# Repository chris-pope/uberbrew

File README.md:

Uber Brewer
=========================

Semi-automated control system for nano breweries.

## Table of Contents

## Hardware

## Software

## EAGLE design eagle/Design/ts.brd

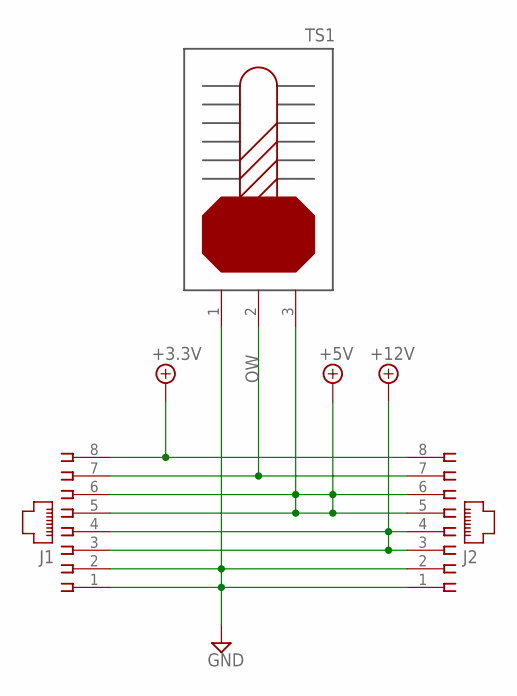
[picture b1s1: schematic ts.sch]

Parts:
J1, J2: 215877-4
TS1: DS18B20; KK-156-3

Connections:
+3P3V: J1.8, J2.8
+5V: J1.5, J1.6, J2.5, J2.6, TS1.3
+12V: J1.3, J1.4, J2.3, J2.4
GND: J1.1, J1.2, J2.1, J2.2, TS1.1
OW: J1.7, J2.7, TS1.2

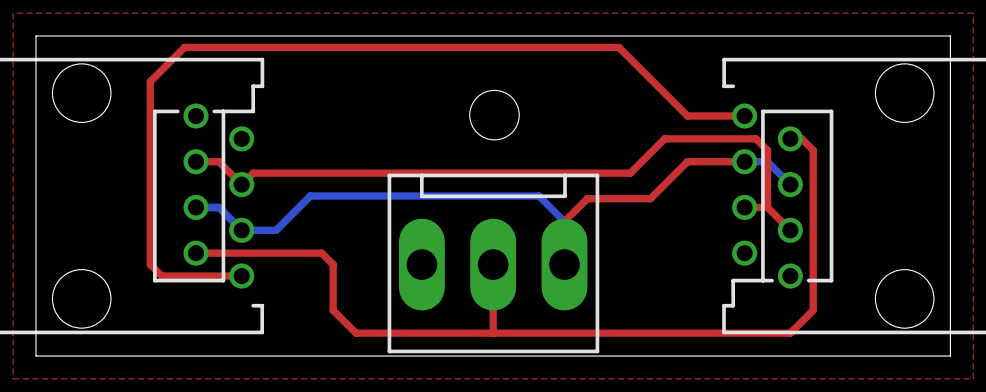
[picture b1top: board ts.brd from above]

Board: 2 copper layers, 50.8 x 17.8 mm, 3 parts (0 on the bottom side), 5 nets.

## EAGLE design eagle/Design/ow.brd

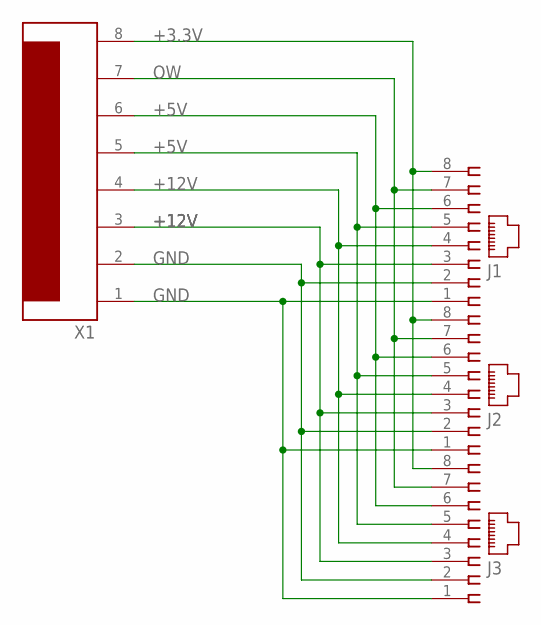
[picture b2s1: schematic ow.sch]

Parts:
J1, J2, J3: 215877-4
X1: 1WIRE-CON; KK-156-8

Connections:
+3.3V: J1.8, J2.8, J3.8, X1.8
+5V: J1.5, J1.6, J2.5, J2.6, J3.5, J3.6, X1.5, X1.6
+12V: J1.3, J1.4, J2.3, J2.4, J3.3, J3.4, X1.3, X1.4
GND: J1.1, J1.2, J2.1, J2.2, J3.1, J3.2, X1.1, X1.2
OW: J1.7, J2.7, J3.7, X1.7

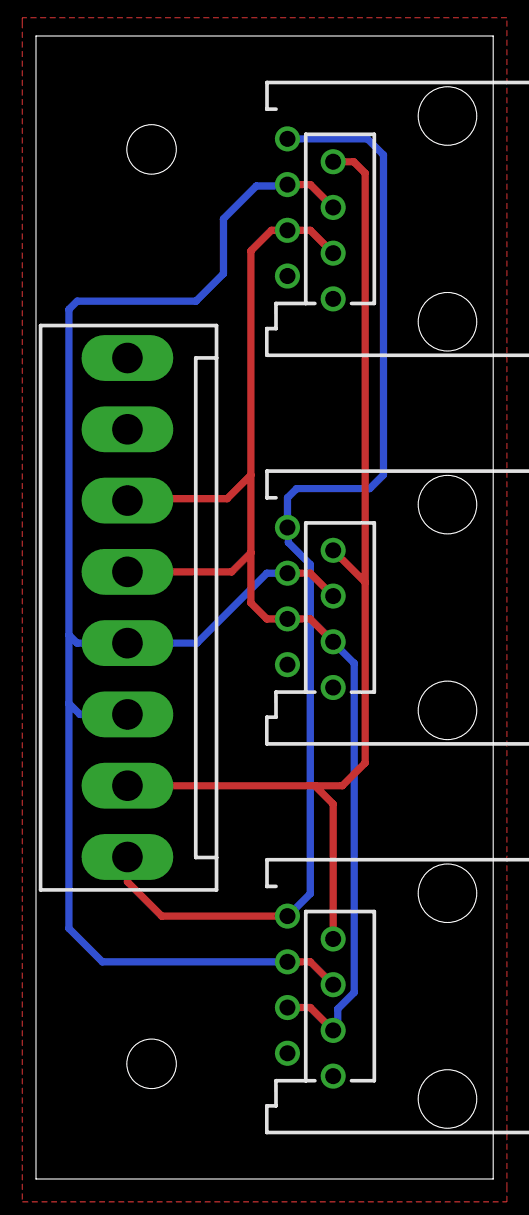
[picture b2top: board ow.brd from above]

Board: 2 copper layers, 25.4 x 63.5 mm, 4 parts (0 on the bottom side), 5 nets.

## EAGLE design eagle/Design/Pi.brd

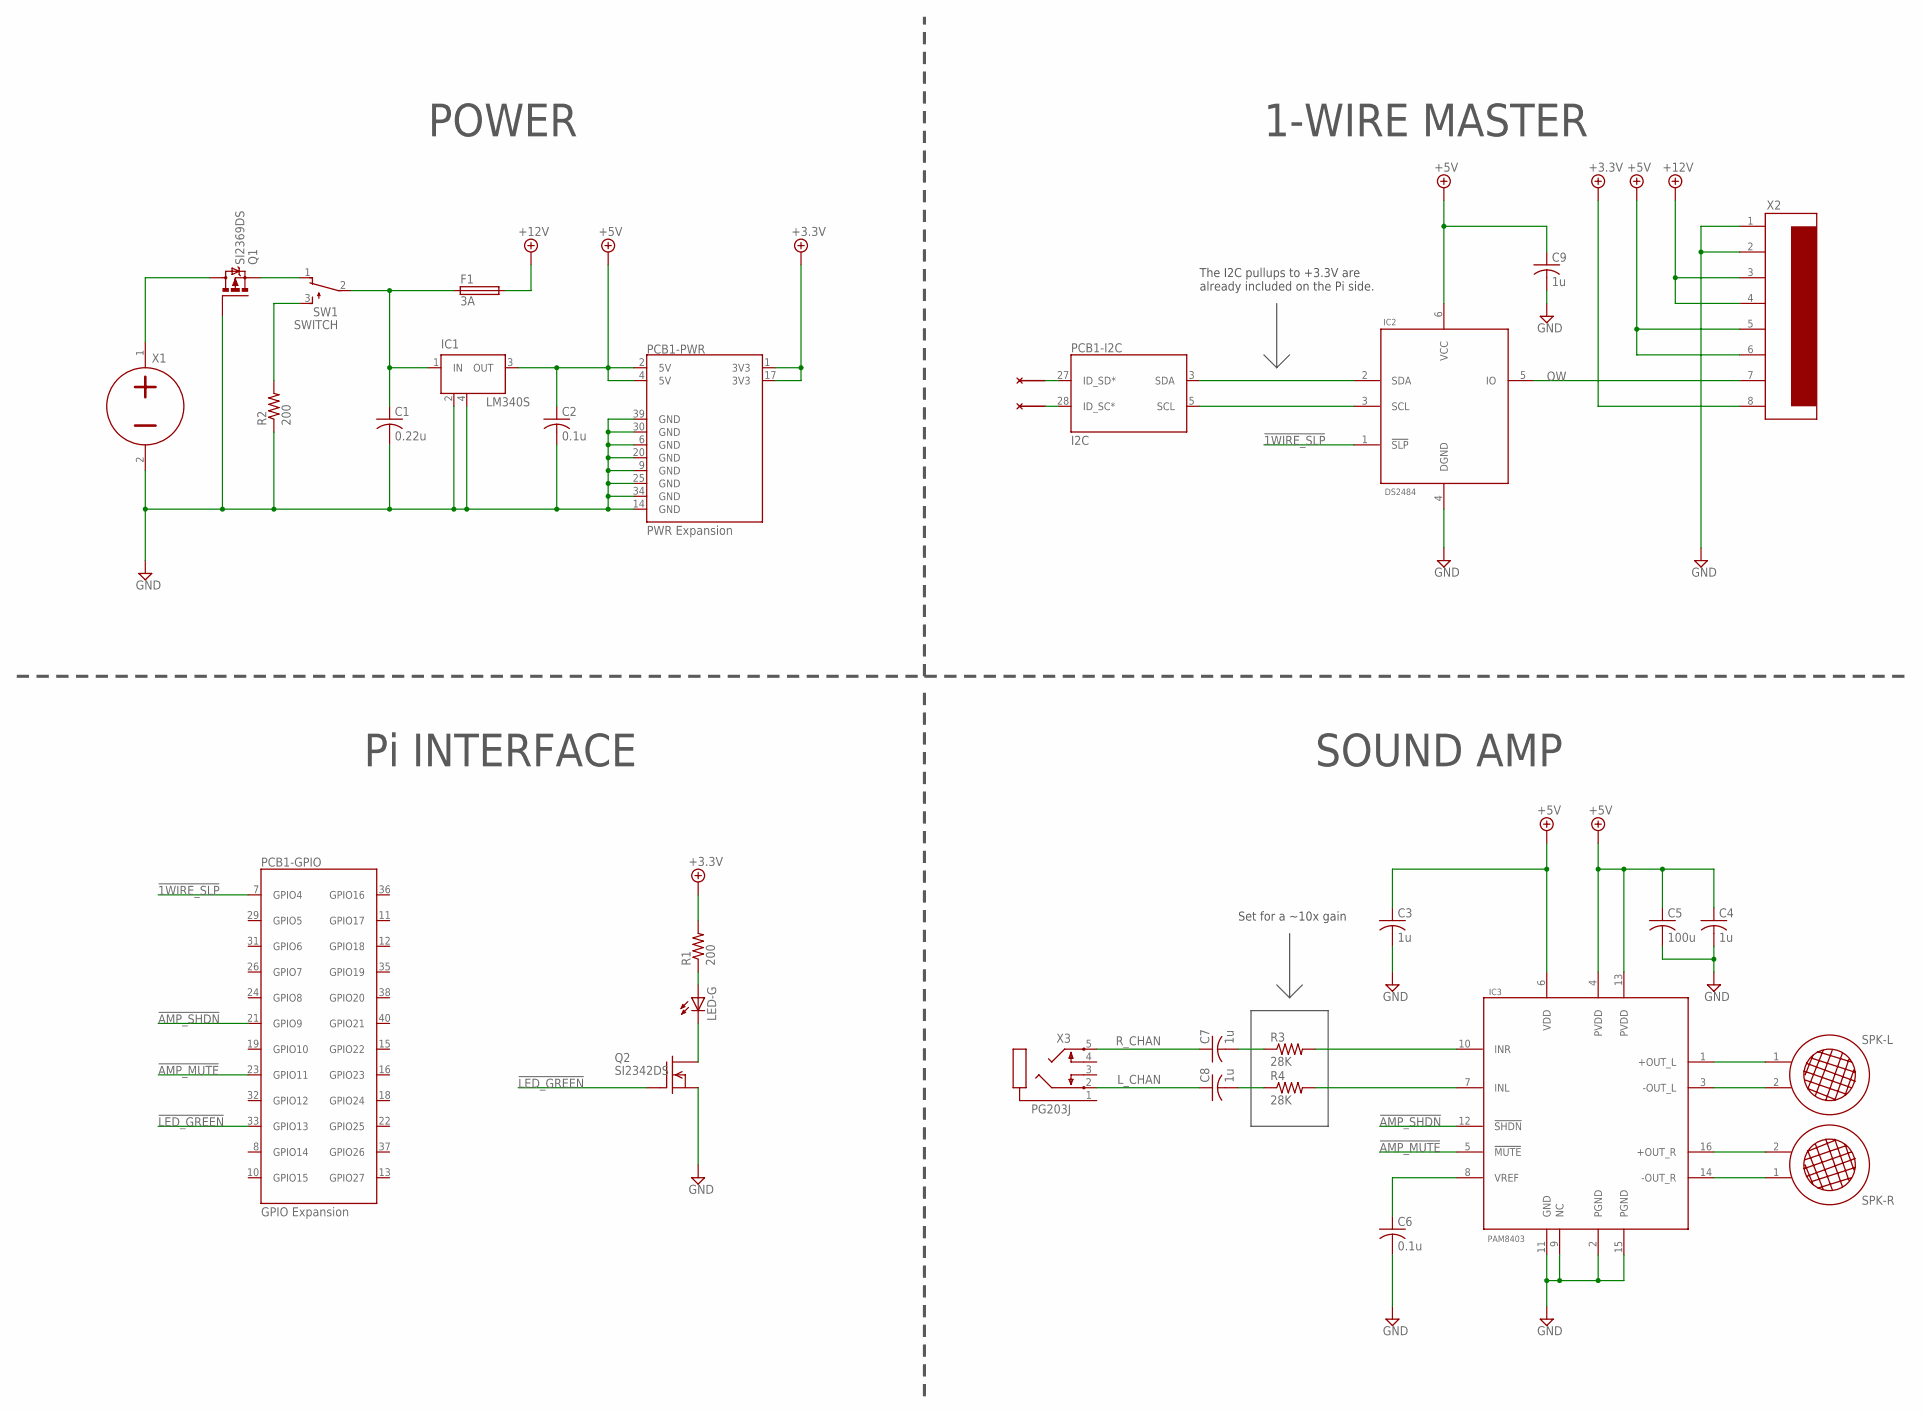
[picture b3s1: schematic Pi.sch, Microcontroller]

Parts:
C1: 0.22u; C0603
C2, C6: 0.1u; C0603
C3, C4, C7, C8, C9: 1u; C0603
C5: 100u; C0805
F1: 3A; F0603
IC1: LM340S; SOT223
IC2: DS2484; SOT23-6L
IC3: PAM8403; SOP16
LED-G: LEDCHIP-LED0603; CHIP-LED0603
PCB1: RPI3
Q1: SI2369DS; SOT23
Q2: SI2342DS; SOT23
R1, R2: 200; R0603
R3, R4: 28K; R0603
SPK-L: SPEAKER; KK-156-2
SPK-R: SPEAKER; KK-156-2
SW1: SWITCH; KK-156-3
X1: SUPPLY_12V; KK-156-2
X2: 1WIRE-CON; KK-156-8
X3: PG203J

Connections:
!1WIRE_SLP: IC2.1 (!SLP), PCB1.7 (GPIO4)
!AMP_MUTE: IC3.5 (!MUTE), PCB1.23 (GPIO11)
!AMP_SHDN: IC3.12 (!SHDN), PCB1.21 (GPIO9)
!LED_GREEN: PCB1.33 (GPIO13), Q2.1 (G)
+3P3V: PCB1.1 (3V3), PCB1.17 (3V3), R1.2, X2.8
+5V: C2.1, C3.1, C4.1, C5.1, C9.1, IC1.3 (OUT), IC2.6 (VCC), IC3.4 (PVDD), IC3.6 (VDD), IC3.13 (PVDD), PCB1.2 (5V), PCB1.4 (5V), X2.5, X2.6
+12V: F1.2, X2.3, X2.4
GND: C1.2, C2.2, C3.2, C4.2, C5.2, C6.2, C9.2, IC1.2 (GND), IC1.4 (GND), IC2.4 (DGND), IC3.2 (PGND), IC3.9 (NC), IC3.11 (GND), IC3.15 (PGND), PCB1.6 (GND), PCB1.9 (GND), PCB1.14 (GND), PCB1.20 (GND), PCB1.25 (GND), PCB1.30 (GND), PCB1.34 (GND), PCB1.39 (GND), Q1.1 (G), Q2.2 (S), R2.1, X1.2, X2.1, X2.2
L_CHAN: C8.1, X3.2
unnamed: LED-G.A, R1.1
unnamed: R2.2, SW1.3 (S)
unnamed: IC2.2 (SDA), PCB1.3 (SDA)
unnamed: IC2.3 (SCL), PCB1.5 (SCL)
unnamed: C6.1, IC3.8 (VREF)
unnamed: Q1.3 (D), X1.1
unnamed: Q1.2 (S), SW1.1 (O)
unnamed: C7.2, R3.1
unnamed: IC3.10 (INR), R3.2
unnamed: C1.1, F1.1, IC1.1 (IN), SW1.2
unnamed: C8.2, R4.1
unnamed: IC3.7 (INL), R4.2
unnamed: IC3.1 (+OUT_L), SPK-L.1
unnamed: IC3.3 (-OUT_L), SPK-L.2
unnamed: IC3.16 (+OUT_R), SPK-R.2
unnamed: IC3.14 (-OUT_R), SPK-R.1
unnamed: LED-G.C, Q2.3 (D)
OW: IC2.5 (IO), X2.7
R_CHAN: C7.1, X3.5

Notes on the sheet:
POWER
Pi INTERFACE
1-WIRE MASTER
The I2C pullups to +3.3V are already included on the Pi side.
Set for a ~10x gain
SOUND AMP

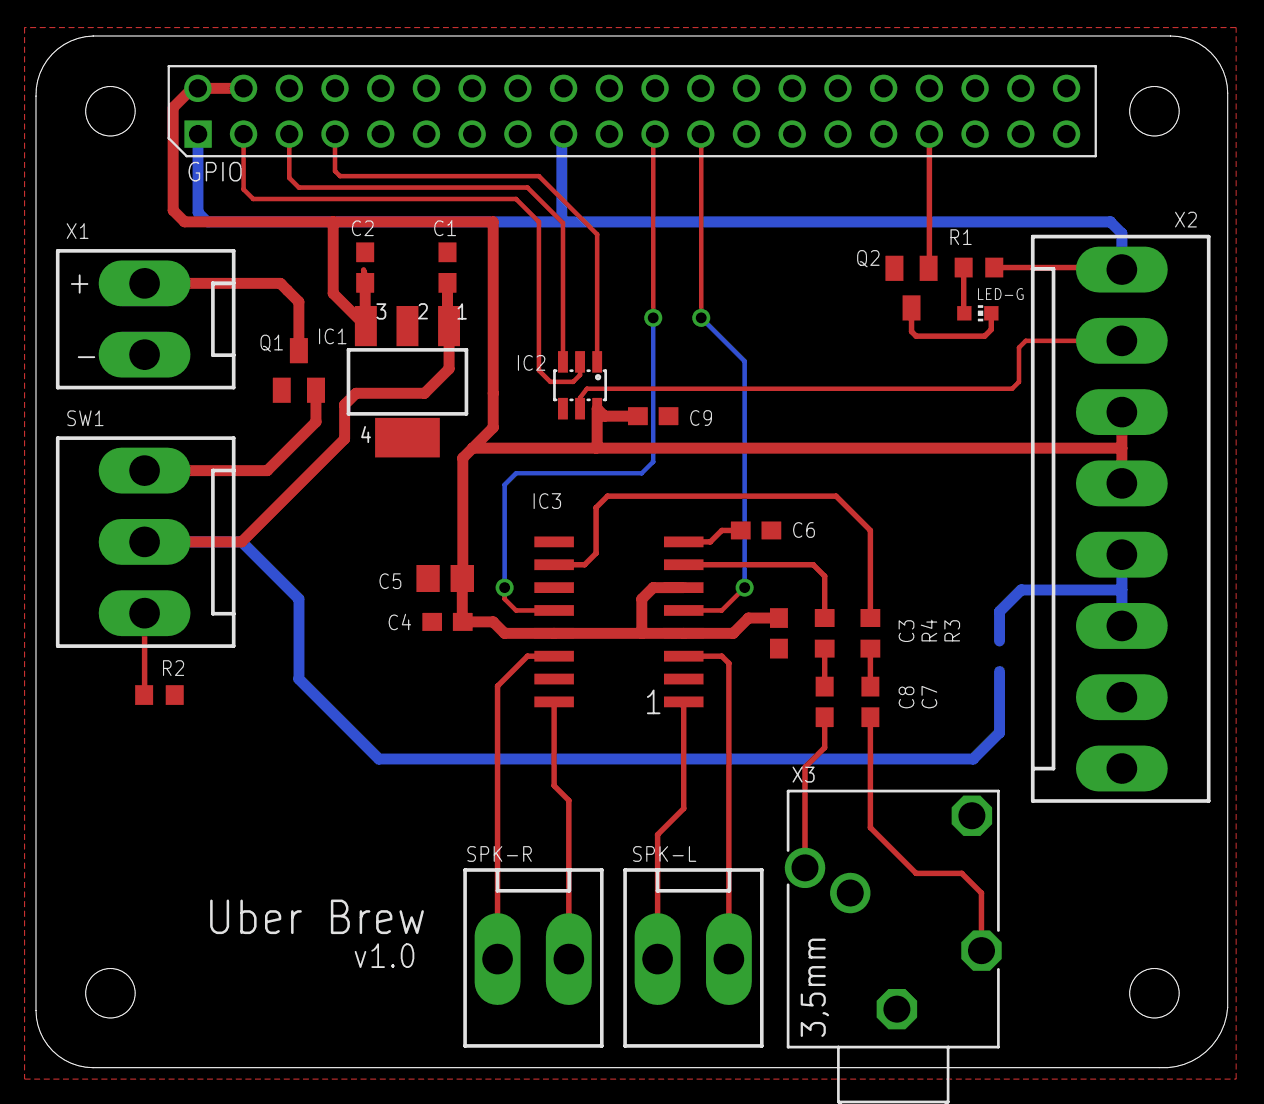
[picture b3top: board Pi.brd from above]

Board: 2 copper layers, 66.2 x 57.3 mm, 27 parts (1 on the bottom side), 28 nets.

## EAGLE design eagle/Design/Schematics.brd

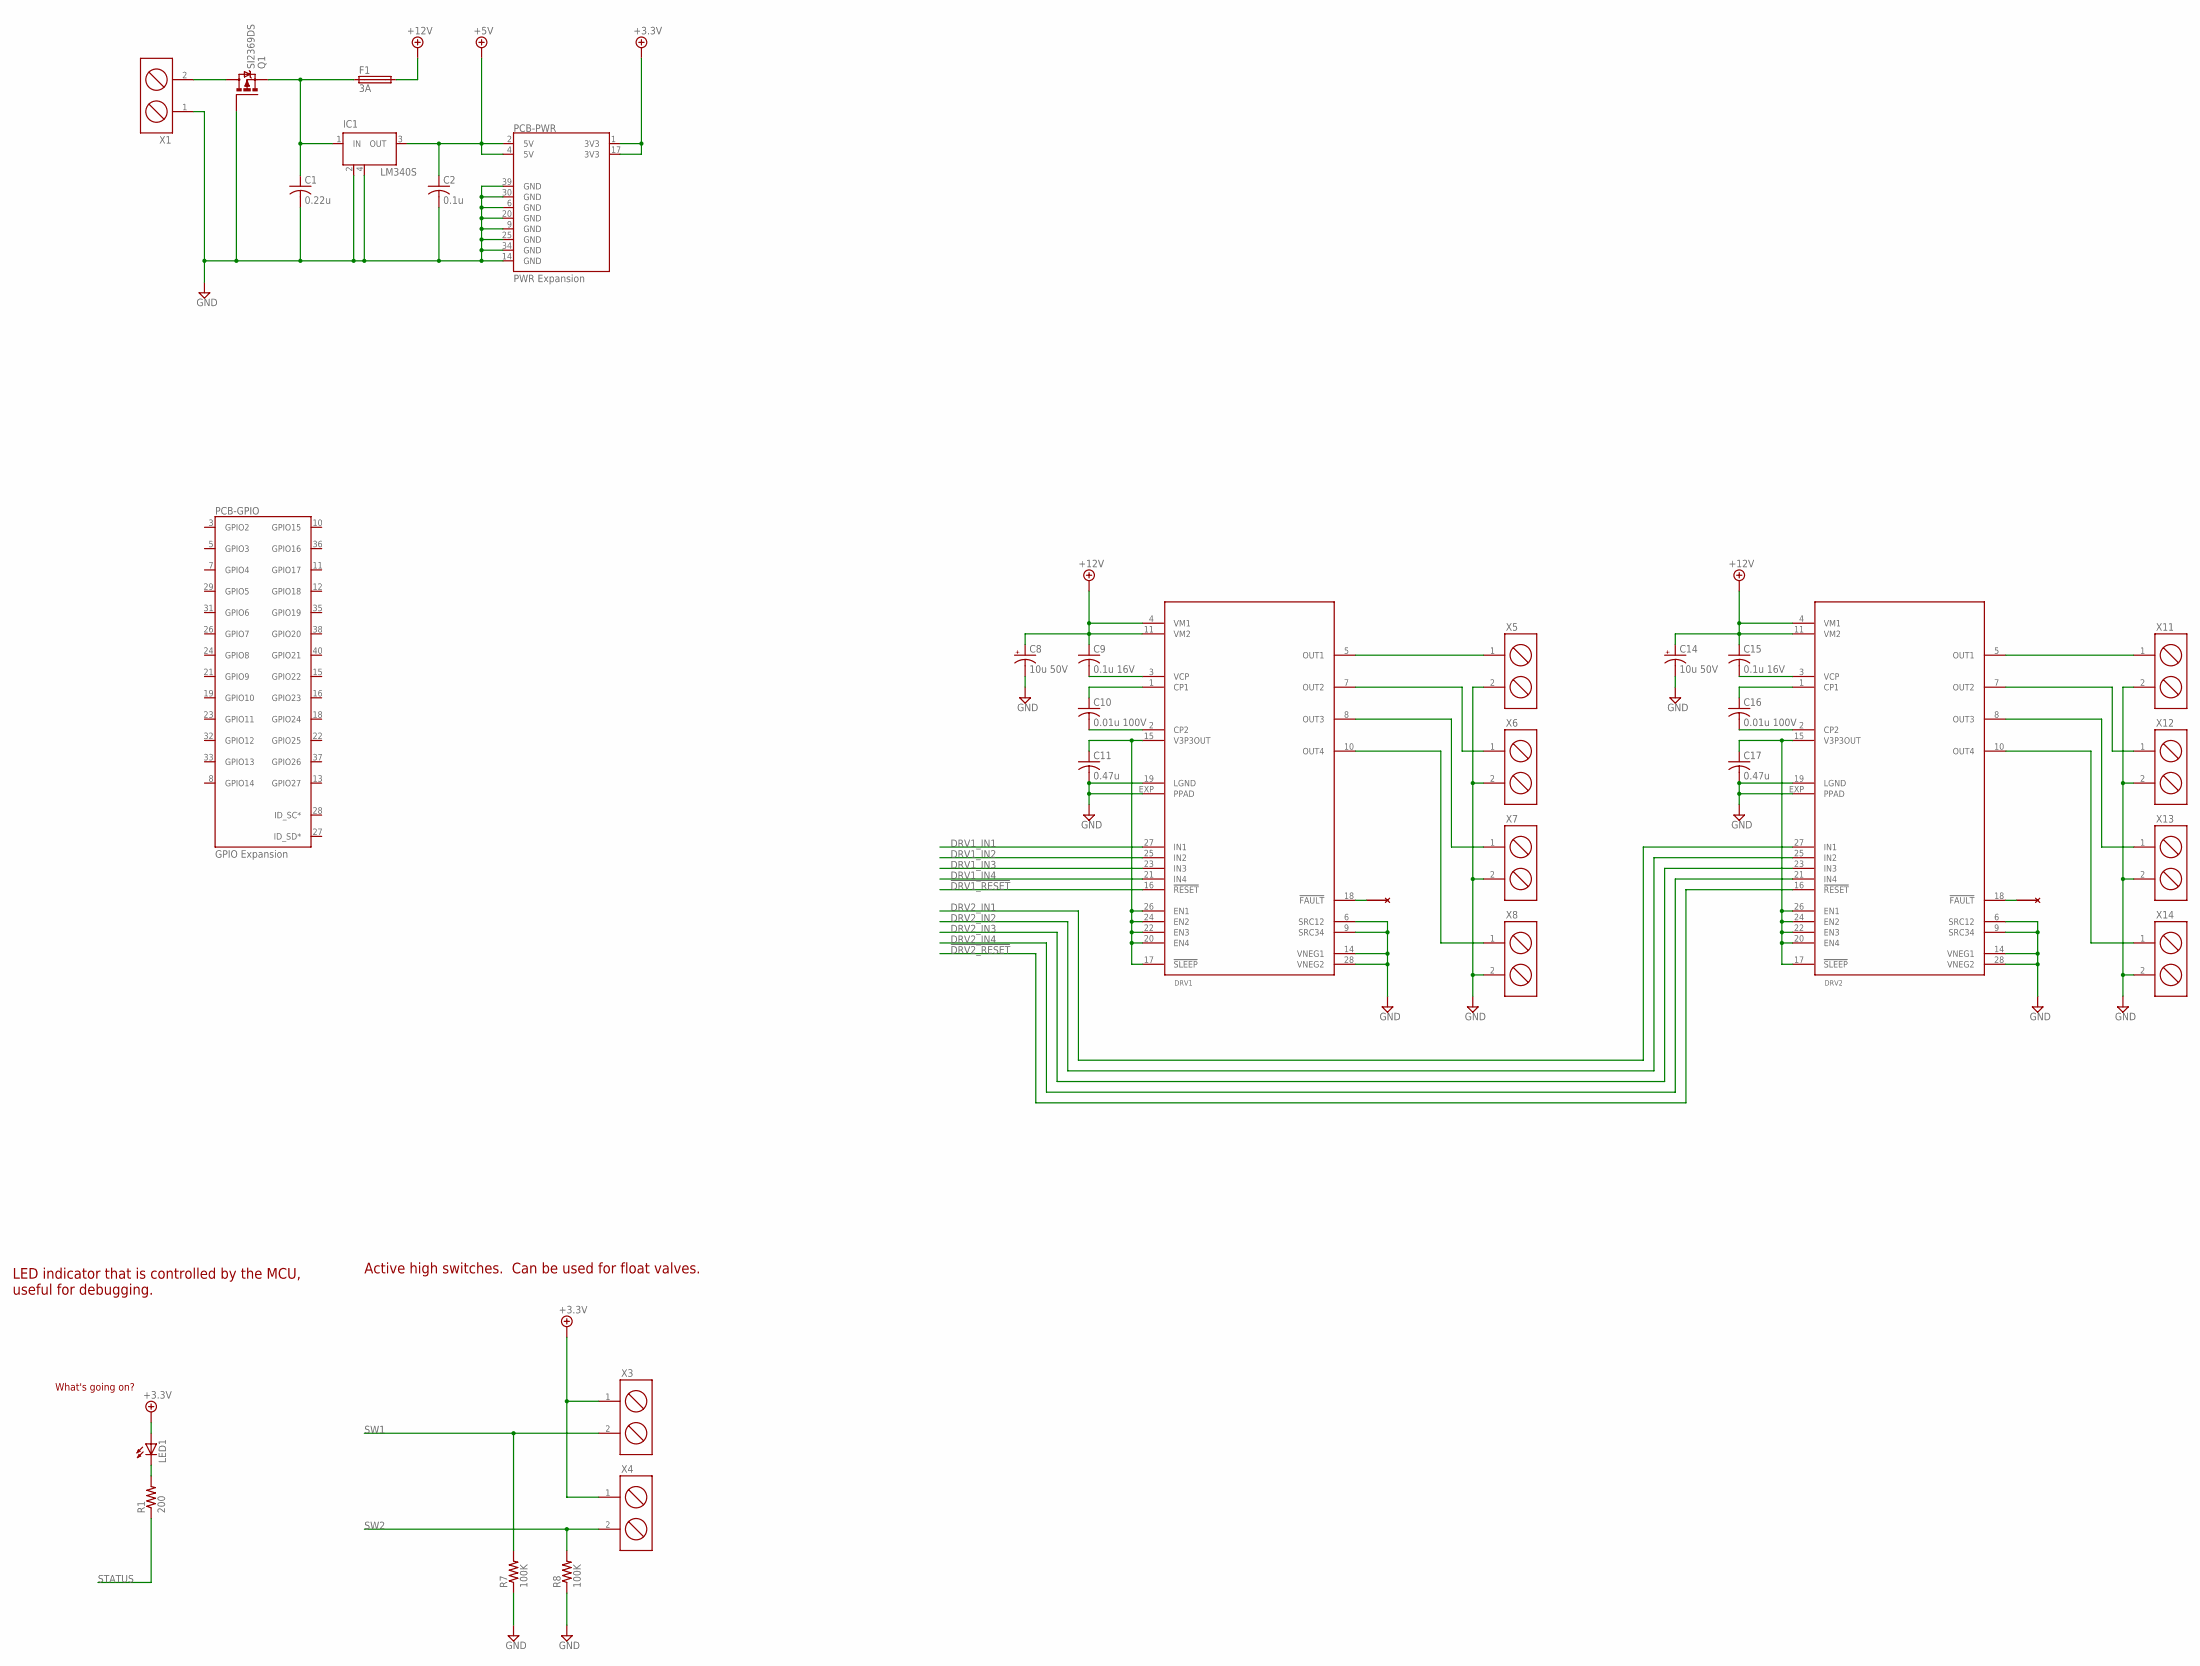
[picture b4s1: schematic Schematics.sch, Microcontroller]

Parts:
C1: 0.22u; C0603
C2: 0.1u; C0603
C8, C14: 10u 50V; TAP5-50
C9, C15: 0.1u 16V; C0603
C10, C16: 0.01u 100V; C0603
C11, C17: 0.47u; C0603
DRV1, DRV2: DRV8844; HTSSOP28PWP
F1: 3A; F0603
IC1: LM340S; SOT223
LED1: LEDCHIP-LED0805; CHIP-LED0805
PCB: RPI3
Q1: SI2369DS; SOT23
R1: 200; R0603
R7, R8: 100K; R0603
X1, X3, X4, X5, X6, X7, X8, X11, X12, X13, X14: MPT2; 2POL254

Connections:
!DRV1_RESET: DRV1.16 (!RESET)
!DRV2_RESET: DRV2.16 (!RESET)
+3P3V: LED1.A, PCB.1 (3V3), PCB.17 (3V3), X3.1, X4.1
+5V: C2.1, IC1.3 (OUT), PCB.2 (5V), PCB.4 (5V)
+12V: C8.+, C9.1, C14.+, C15.1, DRV1.4 (VM1), DRV1.11 (VM2), DRV2.4 (VM1), DRV2.11 (VM2), F1.2
DRV1_IN1: DRV1.27 (IN1)
DRV1_IN2: DRV1.25 (IN2)
DRV1_IN3: DRV1.23 (IN3)
DRV1_IN4: DRV1.21 (IN4)
DRV2_IN1: DRV2.27 (IN1)
DRV2_IN2: DRV2.25 (IN2)
DRV2_IN3: DRV2.23 (IN3)
DRV2_IN4: DRV2.21 (IN4)
GND: C1.2, C2.2, C8.-, C11.2, C14.-, C17.2, DRV1.6 (SRC12), DRV1.9 (SRC34), DRV1.14 (VNEG1), DRV1.19 (LGND), DRV1.28 (VNEG2), DRV1.EXP (PPAD), DRV2.6 (SRC12), DRV2.9 (SRC34), DRV2.14 (VNEG1), DRV2.19 (LGND), DRV2.28 (VNEG2), DRV2.EXP (PPAD), IC1.2 (GND), IC1.4 (GND), PCB.6 (GND), PCB.9 (GND), PCB.14 (GND), PCB.20 (GND), PCB.25 (GND), PCB.30 (GND), PCB.34 (GND), PCB.39 (GND), Q1.1 (G), R7.1, R8.1, X1.1, X5.2, X6.2, X7.2, X8.2, X11.2, X12.2, X13.2, X14.2
unnamed: Q1.3 (D), X1.2
unnamed: C1.1, F1.1, IC1.1 (IN), Q1.2 (S)
unnamed: DRV1.5 (OUT1), X5.1
unnamed: DRV1.7 (OUT2), X6.1
unnamed: DRV1.8 (OUT3), X7.1
unnamed: DRV1.10 (OUT4), X8.1
unnamed: C11.1, DRV1.15 (V3P3OUT), DRV1.17 (!SLEEP), DRV1.20 (EN4), DRV1.22 (EN3), DRV1.24 (EN2), DRV1.26 (EN1)
unnamed: C10.2, DRV1.2 (CP2)
unnamed: C10.1, DRV1.1 (CP1)
unnamed: C9.2, DRV1.3 (VCP)
unnamed: DRV2.5 (OUT1), X11.1
unnamed: DRV2.7 (OUT2), X12.1
unnamed: DRV2.8 (OUT3), X13.1
unnamed: DRV2.10 (OUT4), X14.1
unnamed: C17.1, DRV2.15 (V3P3OUT), DRV2.17 (!SLEEP), DRV2.20 (EN4), DRV2.22 (EN3), DRV2.24 (EN2), DRV2.26 (EN1)
unnamed: LED1.C, R1.2
unnamed: C16.2, DRV2.2 (CP2)
unnamed: C16.1, DRV2.1 (CP1)
unnamed: C15.2, DRV2.3 (VCP)
STATUS: R1.1
SW1: R7.2, X3.2
SW2: R8.2, X4.2

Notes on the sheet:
What's going on?
Active high switches. Can be used for float valves.
LED indicator that is controlled by the MCU, useful for debugging.

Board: 2 copper layers, 31 parts (0 on the bottom side), 25 nets, no tracks yet.

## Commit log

2016-10-24 Added datasheets
    Added datasheets for ICs used in the hardware controller.
2016-10-24 Added gitignore
    Ignore temporary files generated by Eagle.
2016-10-24 Initial commit for the hardware controller
    Schematic view is beta meaning the component list is finalized and the
    only future changes should be netlist related. Board layout is alpha.
    IC placement is roughly fixed but many changes will be needed before it
    is production worthy.
2016-10-25 Added empty Meteor JS app
    Placeholder for where the web interface will be developed.
2016-10-25 Added temporary schematic files to gitignore.
2016-10-25 Routed nets for Temp Sensor #1.
2016-10-26 Goodbye USB, hello Pi
    Completely changed the direction of the hardware development.
    Originally wanted to utilize a USB interface to plug into any PC but
    found it was easier (and cheaper) to by a Raspberry Pi for $35 and build
    an expansion board to control the brew hardware. Created a barebone set
    of schematics and layout.
2016-11-13 Added 1-wire interface.
    The idea is to build a system that can expand as needed by daisy chaning
    pieces together. Instead of having a monolithic controller that has all
    of the functionality it will ever need prebuilt into it, keep it a
    simple controller but provide some kind of network addressing scheme for
    it to commuciate with peripherals. Commercial HVAC systems use 1-wire
    so it should work for our purpose too. This also means peripherals will
2016-11-25 Completed schematic and board routing for Pi controller.
    Assuming I don't find any last minute issues this will be the final
    revision of version 1.0.
2016-11-25 One-Wire expansion board
    Expansion board to connect to the Pi controller to bring the power
    supplies and one-wire data signal to external components.
2016-11-25 Temperature Sensor Peripheral
    Interface for one-wire temperature sensor.
